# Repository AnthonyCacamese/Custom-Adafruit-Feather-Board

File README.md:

This is a Custom PCB designed to integrate Adafruit Feather nRF52840 into a broader electronic system. 
It was designed and tested in the University of Miami Mechanobiology Laboratory in the Summer of 2026 for initial use in a Smart Orthopedic Rehabilitation System.

The board features connections to each pin on the microcontroller using 1x2 Horizontal Molex connectors.
Multiple connections are provided to the 3.3V output and GND pins for greater wiring options.
Various thermal and EMI safety measures are implemented, including thermal relief spokes and via netting.

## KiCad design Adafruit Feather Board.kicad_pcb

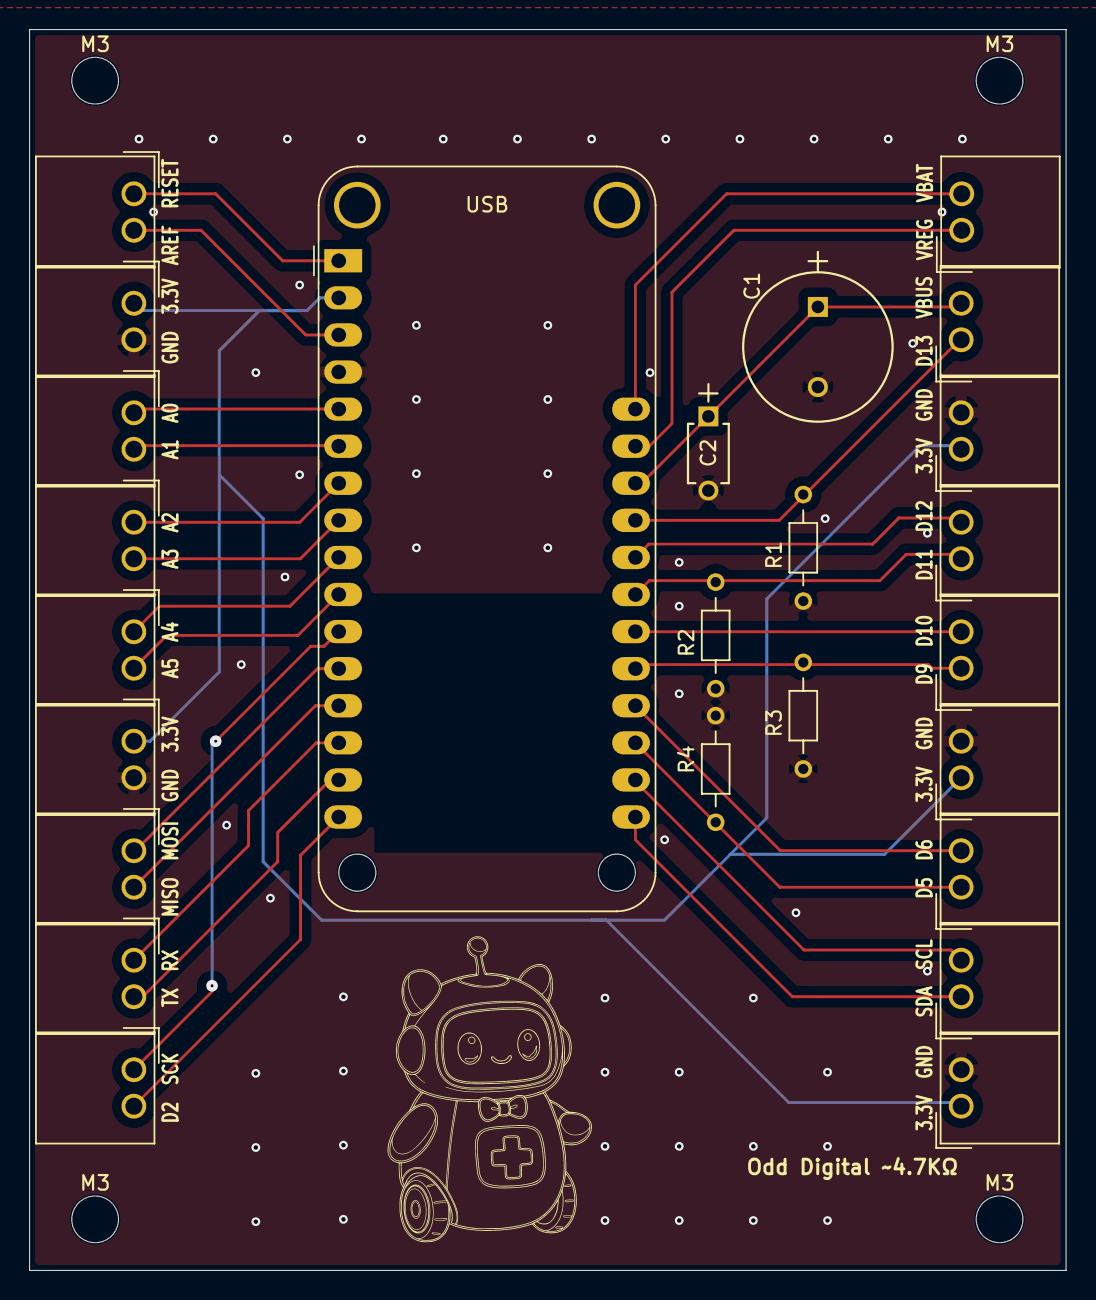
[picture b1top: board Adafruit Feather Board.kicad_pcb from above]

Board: 4 copper layers, 71.0 x 85.0 mm, 29 parts (0 on the bottom side), 28 nets.

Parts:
3.3V  GND, 3.3V  GND#2, 3.3V  GND#3: Molex_SPOX_5268-02A_1x02_P2.50mm_Horizontal
A1  A0, A3  A2, A5  A4: Molex_SPOX_5268-02A_1x02_P2.50mm_Horizontal
AREF  RESET: Molex_SPOX_5268-02A_1x02_P2.50mm_Horizontal
C1: 470 uF; C1_470uF
C2: 0.1 uF; C2_0.1uF
D2  SCK, D5  D6, D9  D10, D11  D12, D13  VBUS: Molex_SPOX_5268-02A_1x02_P2.50mm_Horizontal
GND  3.3V, GND  3.3V#2: Molex_SPOX_5268-02A_1x02_P2.50mm_Horizontal
M3, M3#2, M3#3, M3#4: MountingHole_3.2mm_M3
MISO  MOSI: Molex_SPOX_5268-02A_1x02_P2.50mm_Horizontal
R1, R2, R3, R4: YAG_MF25_YAG; Resistor 4.7K YAGEO
SDA  SCL: Molex_SPOX_5268-02A_1x02_P2.50mm_Horizontal
TX  RX: Molex_SPOX_5268-02A_1x02_P2.50mm_Horizontal
USB: FEATHERWING_NODIM; Adafruit_Feather_WithMountingHoles
VREG  VBAT: Molex_SPOX_5268-02A_1x02_P2.50mm_Horizontal

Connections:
/3.3V: 3.3V GND.1, 3.3V GND#2.1, 3.3V GND#3.1, GND 3.3V.1, GND 3.3V#2.1, USB.2 (3V)
/A0: A1 A0.1, USB.5 (GPIOA0)
/A1: A1 A0.2, USB.6 (GPIOA1)
/A2: A3 A2.1, USB.7 (GPIOA2)
/A3: A3 A2.2, USB.8 (GPIOA3)
/A4: A5 A4.1, USB.9 (GPIOA4)
/A5: A5 A4.2, USB.10 (GPIOA5)
/AREF: AREF RESET.2, USB.3 (AREF)
/D2: D2 SCK.2, USB.16 (NC)
/D5: D5 D6.1, R4.2, USB.19 (GPIO5)
/D6: D5 D6.2, USB.20 (GPIO6)
/D9: D9 D10.1, R3.2, USB.21 (GPIO9)
/D10: D9 D10.2, USB.22 (GPIO10)
/D11: D11 D12.1, R2.2, USB.23 (GPIO11)
/D12: D11 D12.2, USB.24 (GPIO12)
/D13: D13 VBUS.1, R1.2, USB.25 (GPIO13)
/EN: USB.27 (EN), VREG VBAT.1
/MISO: MISO MOSI.2, USB.13 (GPIOMISO)
/MOSI: MISO MOSI.1, USB.12 (GPIOMOSI)
/RESET: AREF RESET.1, USB.1 (~RESET)
/RXD: TX RX.1, USB.14 (GPIORX)
/SCK: D2 SCK.1, USB.11 (GPIOSCK)
/SCL: SDA SCL.2, USB.18 (GPIOSCL)
/SDA: SDA SCL.1, USB.17 (GPIOSDA)
/TXD: TX RX.2, USB.15 (GPIOTX)
GND: 3.3V GND.2, 3.3V GND#2.2, 3.3V GND#3.2, C1.2, C2.2, GND 3.3V.2, GND 3.3V#2.2, R1.1, R2.1, R3.1, R4.1, USB.4 (GND)
unnamed: C1.1, C2.1, D13 VBUS.2, USB.26 (USB)
unnamed: USB.28 (VBAT), VREG VBAT.2
